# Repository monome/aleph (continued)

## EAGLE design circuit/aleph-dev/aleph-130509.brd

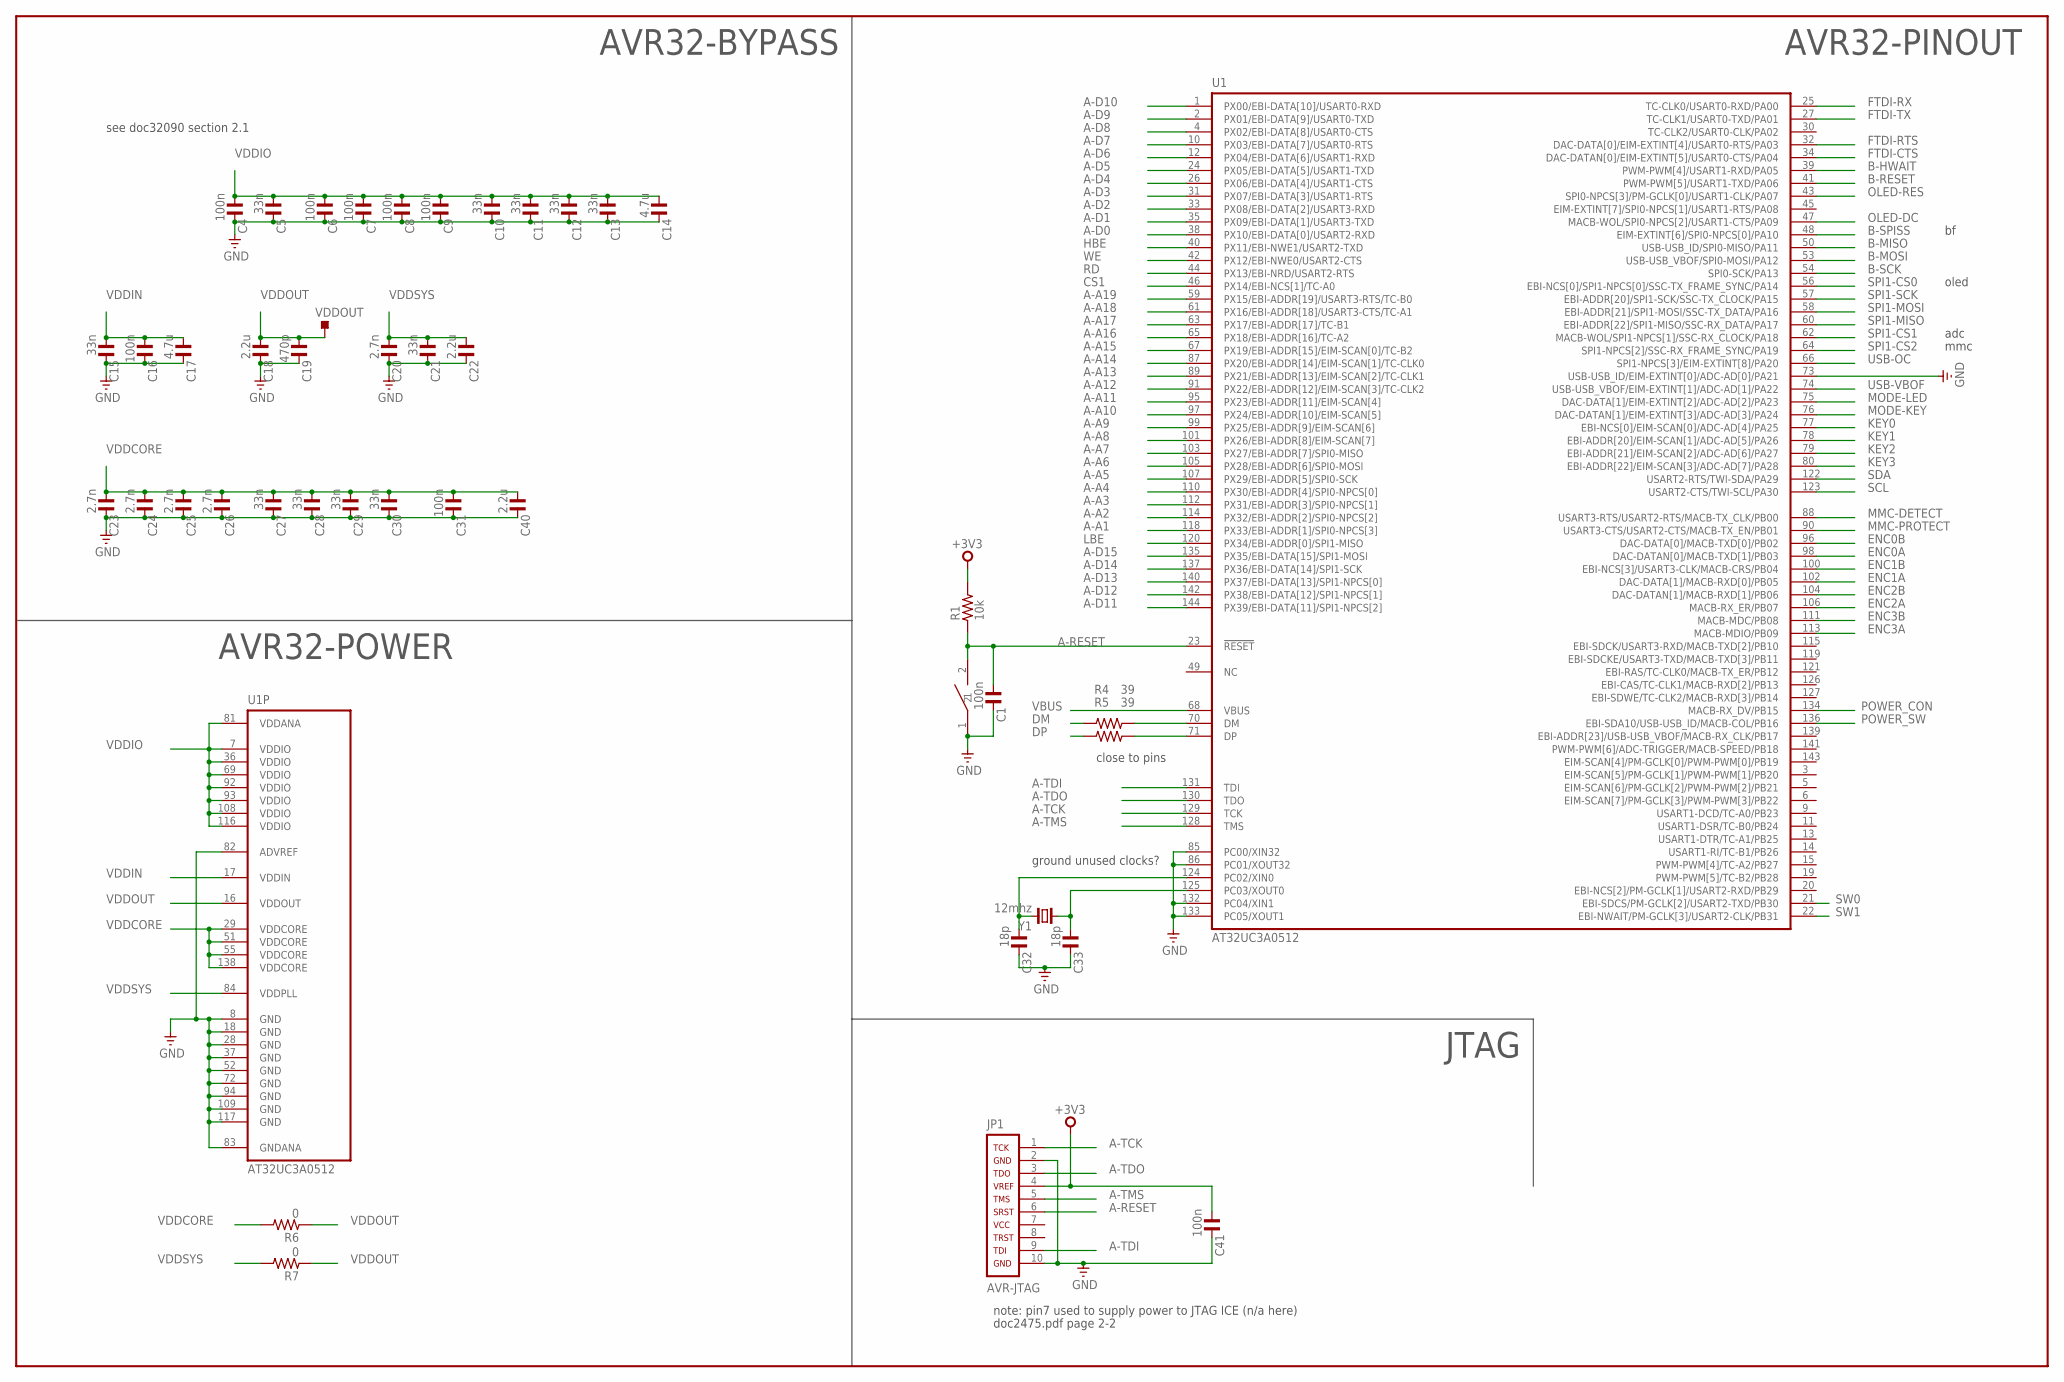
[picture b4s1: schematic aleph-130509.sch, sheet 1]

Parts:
C1, C4, C6, C7, C8, C9, C16, C31, C41: 100n; C0603
C5, C10, C11, C12, C13, C15, C21, C27, C28, C29, C30: 33n; C0603
C14, C17: 4.7u; C1206
C18, C22, C40: 2.2u; C1206
C19: 470p; C0603
C20, C23, C24, C25, C26: 2.7n; C0603
C32, C33: 18p; C0603
JP1: AVR-JTAG; AVR-JTAG-10
R1: 10k; R0603
R4, R5: 39; R0603
R6, R7: 0; R0603
U1: AT32UC3A0512; LQFP144
U$1: PANASONIC-EVQ
VDDOUT: TPS-SMD-10R; SMD-10R
Y1: 12mhz; HC49UP

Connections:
+3V3: C41.1, JP1.4, R1.2; also elsewhere on the board
A-A1: U1.118 (PX33/EBI-ADDR[1]/SPI0-NPCS[3]); also elsewhere on the board
A-A2: U1.114 (PX32/EBI-ADDR[2]/SPI0-NPCS[2]); also elsewhere on the board
A-A3: U1.112 (PX31/EBI-ADDR[3]/SPI0-NPCS[1]); also elsewhere on the board
A-A4: U1.110 (PX30/EBI-ADDR[4]/SPI0-NPCS[0]); also elsewhere on the board
A-A5: U1.107 (PX29/EBI-ADDR[5]/SPI0-SCK); also elsewhere on the board
A-A6: U1.105 (PX28/EBI-ADDR[6]/SPI0-MOSI); also elsewhere on the board
A-A7: U1.103 (PX27/EBI-ADDR[7]/SPI0-MISO); also elsewhere on the board
A-A8: U1.101 (PX26/EBI-ADDR[8]/EIM-SCAN[7]); also elsewhere on the board
A-A9: U1.99 (PX25/EBI-ADDR[9]/EIM-SCAN[6]); also elsewhere on the board
A-A10: U1.97 (PX24/EBI-ADDR[10]/EIM-SCAN[5]); also elsewhere on the board
A-A11: U1.95 (PX23/EBI-ADDR[11]/EIM-SCAN[4]); also elsewhere on the board
A-A12: U1.91 (PX22/EBI-ADDR[12]/EIM-SCAN[3]/TC-CLK2); also elsewhere on the board
A-A13: U1.89 (PX21/EBI-ADDR[13]/EIM-SCAN[2]/TC-CLK1); also elsewhere on the board
A-A14: U1.87 (PX20/EBI-ADDR[14]/EIM-SCAN[1]/TC-CLK0); also elsewhere on the board
A-A15: U1.67 (PX19/EBI-ADDR[15]/EIM-SCAN[0]/TC-B2); also elsewhere on the board
A-A16: U1.65 (PX18/EBI-ADDR[16]/TC-A2); also elsewhere on the board
A-A17: U1.63 (PX17/EBI-ADDR[17]/TC-B1); also elsewhere on the board
A-A18: U1.61 (PX16/EBI-ADDR[18]/USART3-CTS/TC-A1); also elsewhere on the board
A-A19: U1.59 (PX15/EBI-ADDR[19]/USART3-RTS/TC-B0); also elsewhere on the board
A-D0: U1.38 (PX10/EBI-DATA[0]/USART2-RXD); also elsewhere on the board
A-D1: U1.35 (PX09/EBI-DATA[1]/USART3-TXD); also elsewhere on the board
A-D2: U1.33 (PX08/EBI-DATA[2]/USART3-RXD); also elsewhere on the board
A-D3: U1.31 (PX07/EBI-DATA[3]/USART1-RTS); also elsewhere on the board
A-D4: U1.26 (PX06/EBI-DATA[4]/USART1-CTS); also elsewhere on the board
A-D5: U1.24 (PX05/EBI-DATA[5]/USART1-TXD); also elsewhere on the board
A-D6: U1.12 (PX04/EBI-DATA[6]/USART1-RXD); also elsewhere on the board
A-D7: U1.10 (PX03/EBI-DATA[7]/USART0-RTS); also elsewhere on the board
A-D8: U1.4 (PX02/EBI-DATA[8]/USART0-CTS); also elsewhere on the board
A-D9: U1.2 (PX01/EBI-DATA[9]/USART0-TXD); also elsewhere on the board
A-D10: U1.1 (PX00/EBI-DATA[10]/USART0-RXD); also elsewhere on the board
A-D11: U1.144 (PX39/EBI-DATA[11]/SPI1-NPCS[2]); also elsewhere on the board
A-D12: U1.142 (PX38/EBI-DATA[12]/SPI1-NPCS[1]); also elsewhere on the board
A-D13: U1.140 (PX37/EBI-DATA[13]/SPI1-NPCS[0]); also elsewhere on the board
A-D14: U1.137 (PX36/EBI-DATA[14]/SPI1-SCK); also elsewhere on the board
A-D15: U1.135 (PX35/EBI-DATA[15]/SPI1-MOSI); also elsewhere on the board
A-RESET: C1.1, JP1.6, R1.1, U1.23 (!RESET), U$1.2
A-TCK: JP1.1, U1.129 (TCK)
A-TDI: JP1.9, U1.131 (TDI)
A-TDO: JP1.3, U1.130 (TDO)
A-TMS: JP1.5, U1.128 (TMS)
B-HWAIT: U1.39 (PWM-PWM[4]/USART1-RXD/PA05); also elsewhere on the board
B-MISO: U1.50 (USB-USB_ID/SPI0-MISO/PA11); also elsewhere on the board
B-MOSI: U1.53 (USB-USB_VBOF/SPI0-MOSI/PA12); also elsewhere on the board
B-RESET: U1.41 (PWM-PWM[5]/USART1-TXD/PA06); also elsewhere on the board
B-SCK: U1.54 (SPI0-SCK/PA13); also elsewhere on the board
B-SPISS: U1.48 (EIM-EXTINT[6]/SPI0-NPCS[0]/PA10); also elsewhere on the board
CS1: U1.46 (PX14/EBI-NCS[1]/TC-A0); also elsewhere on the board
DM: R4.2; also elsewhere on the board
DP: R5.2; also elsewhere on the board
ENC0A: U1.98 (DAC-DATAN[0]/MACB-TXD[1]/PB03); also elsewhere on the board
ENC0B: U1.96 (DAC-DATA[0]/MACB-TXD[0]/PB02); also elsewhere on the board
ENC1A: U1.102 (DAC-DATA[1]/MACB-RXD[0]/PB05); also elsewhere on the board
ENC1B: U1.100 (EBI-NCS[3]/USART3-CLK/MACB-CRS/PB04); also elsewhere on the board
ENC2A: U1.106 (MACB-RX_ER/PB07); also elsewhere on the board
ENC2B: U1.104 (DAC-DATAN[1]/MACB-RXD[1]/PB06); also elsewhere on the board
ENC3A: U1.113 (MACB-MDIO/PB09); also elsewhere on the board
ENC3B: U1.111 (MACB-MDC/PB08); also elsewhere on the board
FTDI-CTS: U1.34 (DAC-DATAN[0]/EIM-EXTINT[5]/USART0-CTS/P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); also elsewhere on the board
FTDI-RTS: U1.32 (DAC-DATA[0]/EIM-EXTINT[4]/USART0-RTS/PA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); also elsewhere on the board
FTDI-RX: U1.25 (TC-CLK0/USART0-RXD/PA00); also elsewhere on the board
FTDI-TX: U1.27 (TC-CLK1/USART0-TXD/PA01); also elsewhere on the board
GND: C1.2, C4.2, C5.2, C6.2, C7.2, C8.2, C9.2, C10.2, C11.2, C12.2, C13.2, C14.2, C15.2, C16.2, C17.2, C18.2, C19.2, C20.2, C21.2, C22.2, C23.2, C24.2, C25.2, C26.2, C27.2, C28.2, C29.2, C30.2, C31.2, C32.2, C33.2, C40.2, C41.2, JP1.2, JP1.10, U1.8 (GND), U1.18 (GND), U1.28 (GND), U1.37 (GND), U1.52 (GND), U1.72 (GND), U1.73 (USB-USB_ID/EIM-EXTINT[0]/ADC-AD[0]/PA21), U1.82 (ADVREF), U1.83 (GNDANA), U1.85 (PC00/XIN32), U1.86 (PC01/XOUT32), U1.94 (GND), U1.109 (GND), U1.117 (GND), U1.132 (PC04/XIN1), U1.133 (PC05/XOUT1), U$1.1; also elsewhere on the board
HBE: U1.40 (PX11/EBI-NWE1/USART2-TXD); also elsewhere on the board
KEY0: U1.77 (EBI-NCS[0]/EIM-SCAN[0]/ADC-AD[4]/PA25); also elsewhere on the board
KEY1: U1.78 (EBI-ADDR[20]/EIM-SCAN[1]/ADC-AD[5]/PA26); also elsewhere on the board
KEY2: U1.79 (EBI-ADDR[21]/EIM-SCAN[2]/ADC-AD[6]/PA27); also elsewhere on the board
KEY3: U1.80 (EBI-ADDR[22]/EIM-SCAN[3]/ADC-AD[7]/PA28); also elsewhere on the board
LBE: U1.120 (PX34/EBI-ADDR[0]/SPI1-MISO); also elsewhere on the board
MMC-DETECT: U1.88 (USART3-RTS/USART2-RTS/MACB-TX_CLK/PB00); also elsewhere on the board
MMC-PROTECT: U1.90 (USART3-CTS/USART2-CTS/MACB-TX_EN/PB01); also elsewhere on the board
MODE-KEY: U1.76 (DAC-DATAN[1]/EIM-EXTINT[3]/ADC-AD[3]/PA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); also elsewhere on the board
MODE-LED: U1.75 (DAC-DATA[1]/EIM-EXTINT[2]/ADC-AD[2]/PA23); also elsewhere on the board
unnamed: C32.1, U1.124 (PC02/XIN0), Y1.2
unnamed: C33.1, U1.125 (PC03/XOUT0), Y1.1
unnamed: R4.1, U1.70 (DM)
unnamed: R5.1, U1.71 (DP)
OLED-DC: U1.47 (MACB-WOL/SPI0-NPCS[2]/USART1-CTS/PA09); also elsewhere on the board
OLED-RES: U1.43 (SPI0-NPCS[3]/PM-GCLK[0]/USART1-CLK/PA07); also elsewhere on the board
POWER_CON: U1.134 (MACB-RX_DV/PB15); also elsewhere on the board
POWER_SW: U1.136 (EBI-SDA10/USB-USB_ID/MACB-COL/PB16); also elsewhere on the board
RD: U1.44 (PX13/EBI-NRD/USART2-RTS); also elsewhere on the board
SCL: U1.123 (USART2-CTS/TWI-SCL/PA30); also elsewhere on the board
SDA: U1.122 (USART2-RTS/TWI-SDA/PA29); also elsewhere on the board
SPI1-CS0: U1.56 (EBI-NCS[0]/SPI1-NPCS[0]/SSC-TX_FRAME_SY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); also elsewhere on the board
SPI1-CS1: U1.62 (MACB-WOL/SPI1-NPCS[1]/SSC-RX_CLOCK/PA18); also elsewhere on the board
SPI1-CS2: U1.64 (SPI1-NPCS[2]/SSC-RX_FRAME_SYNC/PA19); also elsewhere on the board
SPI1-MISO: U1.60 (EBI-ADDR[22]/SPI1-MISO/SSC-RX_DATA/PA17); also elsewhere on the board
SPI1-MOSI: U1.58 (EBI-ADDR[21]/SPI1-MOSI/SSC-TX_DATA/PA16); also elsewhere on the board
SPI1-SCK: U1.57 (EBI-ADDR[20]/SPI1-SCK/SSC-TX_CLOCK/PA15); also elsewhere on the board
SW0: U1.21 (EBI-SDCS/PM-GCLK[2]/USART2-TXD/PB30); also elsewhere on the board
SW1: U1.22 (EBI-NWAIT/PM-GCLK[3]/USART2-CLK/PB31); also elsewhere on the board
USB-OC: U1.66 (SPI1-NPCS[3]/EIM-EXTINT[8]/PA20); also elsewhere on the board
USB-VBOF: U1.74 (USB-USB_VBOF/EIM-EXTINT[1]/ADC-AD[1]/PA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); also elsewhere on the board
VBUS: U1.68 (VBUS); also elsewhere on the board
VDDCORE: C23.1, C24.1, C25.1, C26.1, C27.1, C28.1, C29.1, C30.1, C31.1, C40.1, R6.2, U1.29 (VDDCORE), U1.51 (VDDCORE), U1.55 (VDDCORE), U1.138 (VDDCORE)
VDDIN: C15.1, C16.1, C17.1, U1.17 (VDDIN); also elsewhere on the board
VDDIO: C4.1, C5.1, C6.1, C7.1, C8.1, C9.1, C10.1, C11.1, C12.1, C13.1, C14.1, U1.7 (VDDIO), U1.36 (VDDIO), U1.69 (VDDIO), U1.81 (VDDANA), U1.92 (VDDIO), U1.93 (VDDIO), U1.108 (VDDIO), U1.116 (VDDIO); also elsewhere on the board
VDDOUT: C18.1, C19.1, R6.1, R7.1, U1.16 (VDDOUT), VDDOUT.TP
VDDSYS: C20.1, C21.1, C22.1, R7.2, U1.84 (VDDPLL)
WE: U1.42 (PX12/EBI-NWE0/USART2-CTS); also elsewhere on the board

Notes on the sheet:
note: pin7 used to supply power to JTAG ICE (n/a here)
doc2475.pdf page 2-2
ground unused clocks?
close to pins
see doc32090 section 2.1
mmc
adc
JTAG
AVR32-POWER
AVR32-BYPASS
AVR32-PINOUT
oled

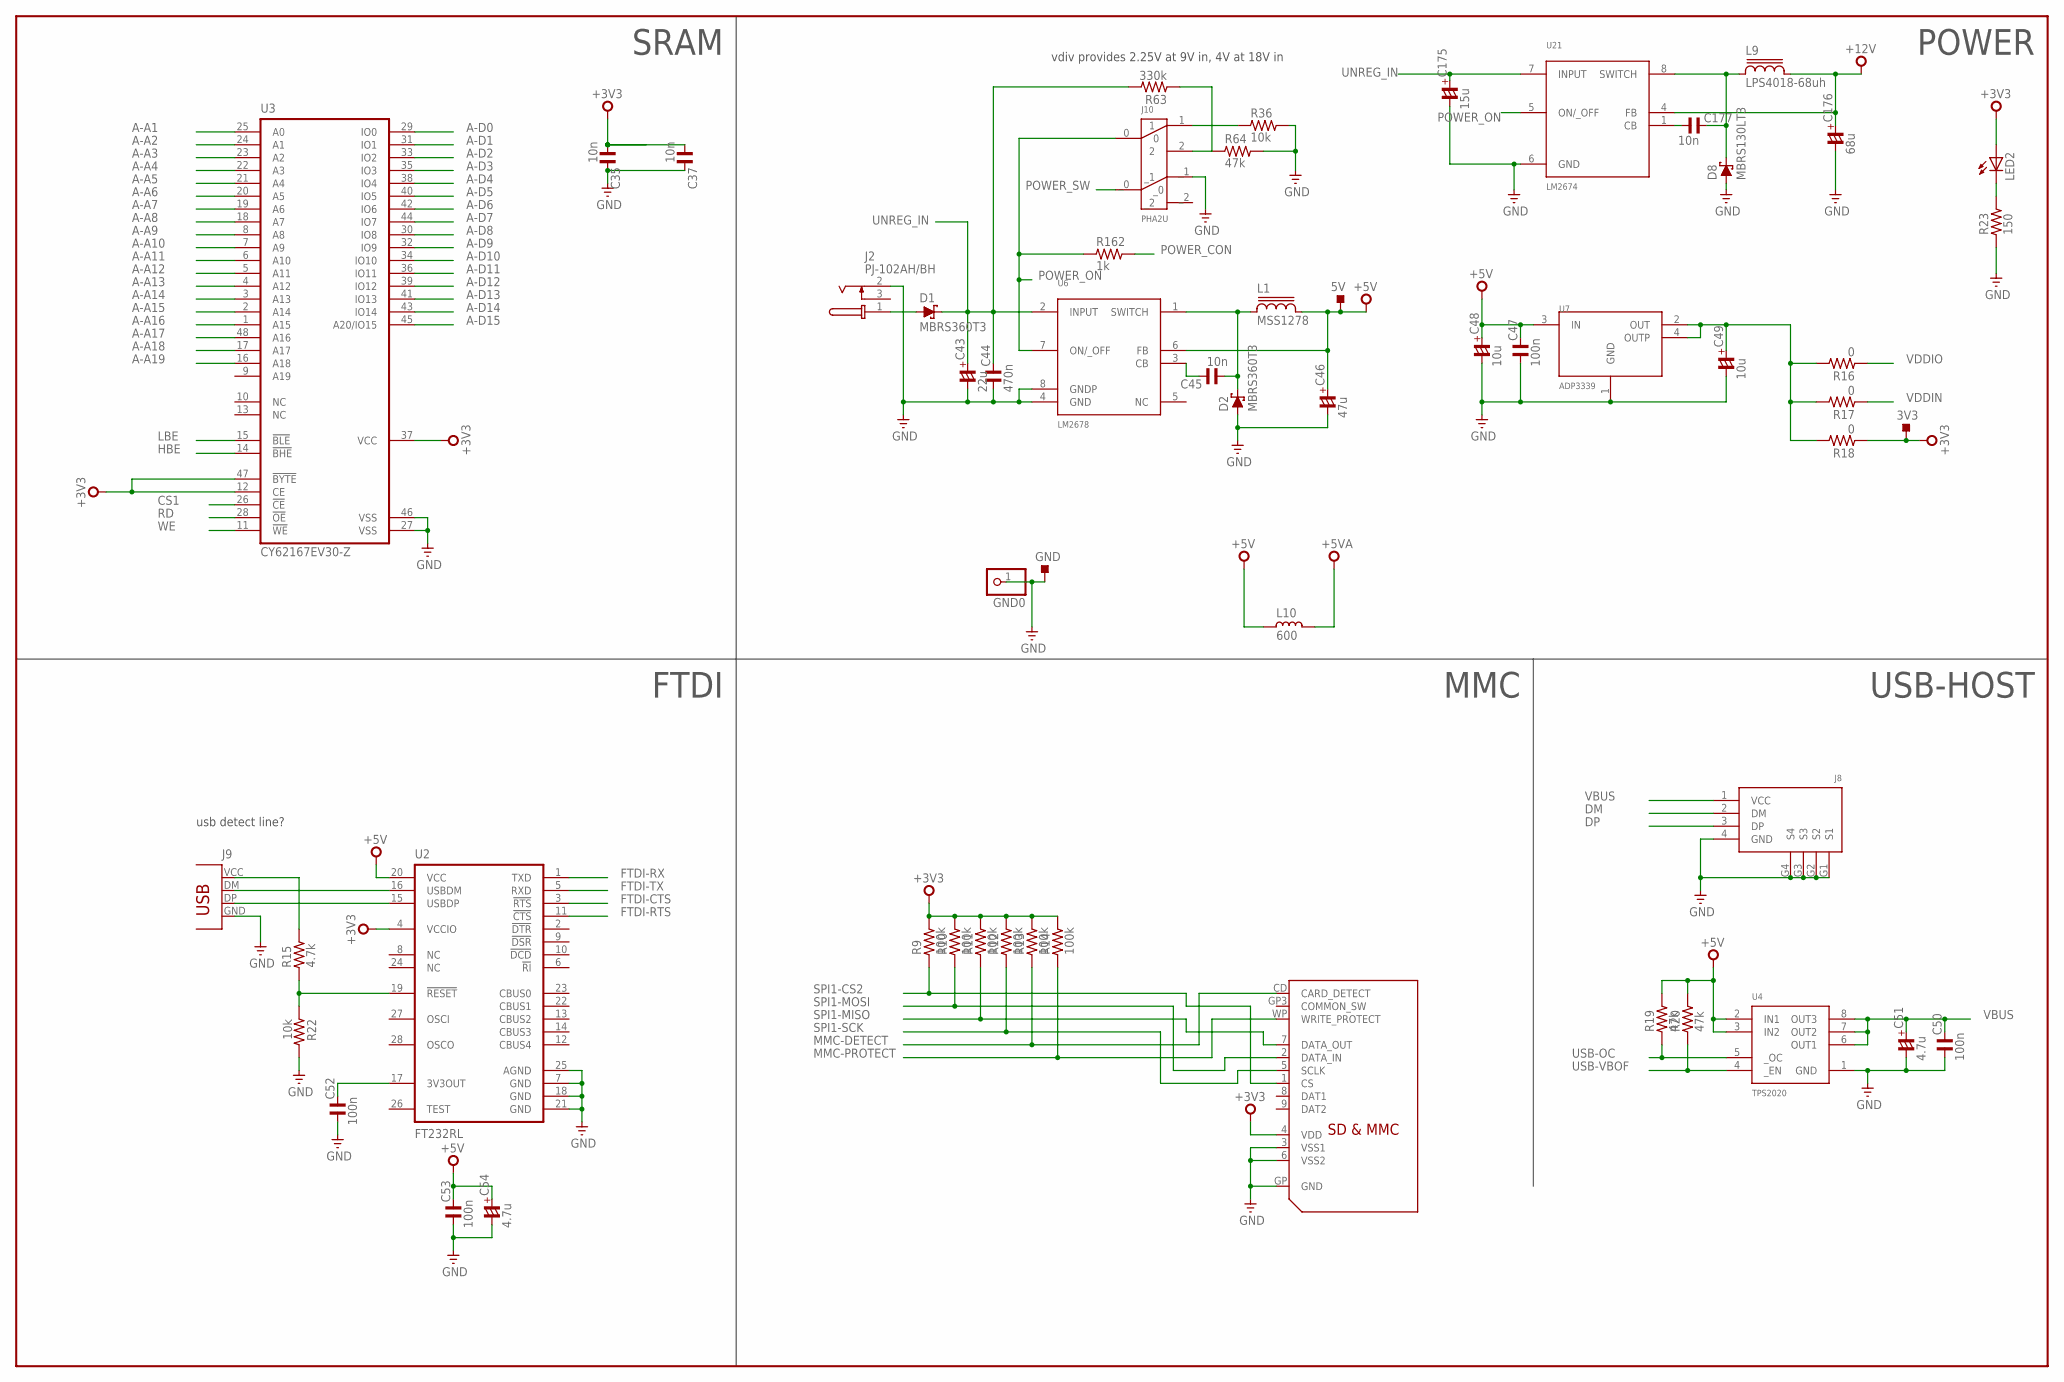
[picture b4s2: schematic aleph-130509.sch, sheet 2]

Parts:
3V3, 5V: TPS-SMD-15R; SMD-15R
C35, C37, C177: 10n; C0603
C43: 22u; C1206/T
C44: 470n; C1206
C45: 10n; C1206
C46: 47u; C3528/T
C47: 100n; C1206
C48, C49: 10u; C1206/T
C50, C52, C53: 100n; C0603
C51, C54: 4.7u; C1206/T
C175: 15u; C6032/T
C176: 68u; C7343/T
D1, D2: MBRS360T3; SMC
D8: MBRS130LT3; SMB403A
GND: TPS-SMD-20R; SMD-20R
GND0: PINHD-1X1; 1X01
J2: PJ-102AH/BH; PJ-102XH
J8: USBA-VERT
J9: USB_TYPE_B; USB_B
J10: PHA2U
L1: MSS1278
L9: LPS4018-68uh; LPS4018
L10: 600; L1206
LED2: LEDCHIPLED_1206; CHIPLED_1206
R9, R10, R11, R12, R13, R14: 100k; R0603
R15: 4.7k; R0603
R16, R17, R18: 0; R0603
R19, R20, R64: 47k; R0603
R22, R36: 10k; R0603
R23: 150; R0603
R63: 330k; R0603
R162: 1k; R0603
U2: FT232RL; SSOP28
U3: CY62167EV30-Z; TSOP48
U4: TPS2020; SO08
U6: LM2678; TO263-7
U7: ADP3339; SOT223
U21: LM2674; SO08
U$6: SDMMC06132; 06132

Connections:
+3V3: 3V3.TP, C35.1, C37.1, LED2.A, R9.2, R10.2, R11.2, R12.2, R13.2, R14.2, R18.1, U2.4 (VCCIO), U3.12 (CE), U3.37 (VCC), U3.47 (!BYTE!), U$6.4 (VDD); also elsewhere on the board
+5V: 5V.TP, C46.+, C47.2, C48.+, C53.2, C54.+, L1.2, L10.2, R19.2, R20.2, U2.20 (VCC), U4.2 (IN1), U4.3 (IN2), U6.6 (FB), U7.3 (IN); also elsewhere on the board
+5VA: L10.1; also elsewhere on the board
+12V: C176.+, L9.2, U21.4 (FB); also elsewhere on the board
A-A1: U3.25 (A0); also elsewhere on the board
A-A2: U3.24 (A1); also elsewhere on the board
A-A3: U3.23 (A2); also elsewhere on the board
A-A4: U3.22 (A3); also elsewhere on the board
A-A5: U3.21 (A4); also elsewhere on the board
A-A6: U3.20 (A5); also elsewhere on the board
A-A7: U3.19 (A6); also elsewhere on the board
A-A8: U3.18 (A7); also elsewhere on the board
A-A9: U3.8 (A8); also elsewhere on the board
A-A10: U3.7 (A9); also elsewhere on the board
A-A11: U3.6 (A10); also elsewhere on the board
A-A12: U3.5 (A11); also elsewhere on the board
A-A13: U3.4 (A12); also elsewhere on the board
A-A14: U3.3 (A13); also elsewhere on the board
A-A15: U3.2 (A14); also elsewhere on the board
A-A16: U3.1 (A15); also elsewhere on the board
A-A17: U3.48 (A16); also elsewhere on the board
A-A18: U3.17 (A17); also elsewhere on the board
A-A19: U3.16 (A18); also elsewhere on the board
A-D0: U3.29 (IO0); also elsewhere on the board
A-D1: U3.31 (IO1); also elsewhere on the board
A-D2: U3.33 (IO2); also elsewhere on the board
A-D3: U3.35 (IO3); also elsewhere on the board
A-D4: U3.38 (IO4); also elsewhere on the board
A-D5: U3.40 (IO5); also elsewhere on the board
A-D6: U3.42 (IO6); also elsewhere on the board
A-D7: U3.44 (IO7); also elsewhere on the board
A-D8: U3.30 (IO8); also elsewhere on the board
A-D9: U3.32 (IO9); also elsewhere on the board
A-D10: U3.34 (IO10); also elsewhere on the board
A-D11: U3.36 (IO11); also elsewhere on the board
A-D12: U3.39 (IO12); also elsewhere on the board
A-D13: U3.41 (IO13); also elsewhere on the board
A-D14: U3.43 (IO14); also elsewhere on the board
A-D15: U3.45 (A20/IO15); also elsewhere on the board
CS1: U3.26 (!CE!); also elsewhere on the board
DM: J8.2 (DM); also elsewhere on the board
DP: J8.3 (DP); also elsewhere on the board
FTDI-CTS: U2.3 (!RTS!); also elsewhere on the board
FTDI-RTS: U2.11 (!CTS!); also elsewhere on the board
FTDI-RX: U2.1 (TXD); also elsewhere on the board
FTDI-TX: U2.5 (RXD); also elsewhere on the board
GND: C35.2, C37.2, C43.-, C44.1, C46.-, C47.1, C48.-, C49.-, C50.1, C51.-, C52.1, C53.1, C54.-, C175.-, C176.-, D2.A, D8.A, GND.TP, GND0.1, J2.2 (S), J8.4 (GND), J8.G1 (S1), J8.G2 (S2), J8.G3 (S3), J8.G4 (S4), J9.GND, J10._1, R22.2, R23.1, R36.2, R64.2, U2.7 (GND), U2.18 (GND), U2.21 (GND), U2.25 (AGND), U3.27 (VSS), U3.46 (VSS), U4.1 (GND), U6.4 (GND), U6.8 (GNDP), U7.1 (GND), U21.6 (GND), U$6.3 (VSS1), U$6.6 (VSS2), U$6.GP (GND); also elsewhere on the board
HBE: U3.14 (!BHE!); also elsewhere on the board
LBE: U3.15 (!BLE!); also elsewhere on the board
MMC-DETECT: R13.1, U$6.CD (CARD_DETECT); also elsewhere on the board
MMC-PROTECT: R14.1, U$6.WP (WRITE_PROTECT); also elsewhere on the board
unnamed: D1.A, J2.1 (T)
unnamed: R15.1, R22.1, U2.19 (!RESET!)
unnamed: C45.1, D2.C, L1.1, U6.1 (SWITCH)
unnamed: C45.2, U6.3 (CB)
unnamed: J9.DM (USBDM), U2.16 (USBDM)
unnamed: J9.DP (USBDP), U2.15 (USBDP)
unnamed: C52.2, U2.17 (3V3OUT)
unnamed: LED2.C, R23.2
unnamed: J9.VCC, R15.2
unnamed: C49.+, R16.2, R17.2, R18.2, U7.2 (OUT), U7.4 (OUTP)
unnamed: J10.1, R36.1
unnamed: J10.2, R63.1, R64.1
unnamed: C177.1, U21.1 (CB)
unnamed: C177.2, D8.C, L9.1, U21.8 (SWITCH)
POWER_CON: R162.2; also elsewhere on the board
POWER_ON: J10.0, R162.1, U6.7 (ON/_OFF), U21.5 (ON/_OFF)
POWER_SW: J10._0; also elsewhere on the board
RD: U3.28 (!OE!); also elsewhere on the board
SPI1-CS2: R9.1, U$6.1 (CS); also elsewhere on the board
SPI1-MISO: R11.1, U$6.7 (DATA_OUT); also elsewhere on the board
SPI1-MOSI: R10.1, U$6.2 (DATA_IN); also elsewhere on the board
SPI1-SCK: R12.1, U$6.5 (SCLK); also elsewhere on the board
UNREG_IN: C43.+, C44.2, C175.+, D1.C, R63.2, U6.2 (INPUT), U21.7 (INPUT)
USB-OC: R19.1, U4.5 (_OC); also elsewhere on the board
USB-VBOF: R20.1, U4.4 (_EN); also elsewhere on the board
VBUS: C50.2, C51.+, J8.1 (VCC), U4.6 (OUT1), U4.7 (OUT2), U4.8 (OUT3); also elsewhere on the board
VDDIN: R17.1; also elsewhere on the board
VDDIO: R16.1; also elsewhere on the board
WE: U3.11 (!WE!); also elsewhere on the board

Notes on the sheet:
usb detect line?
SRAM
MMC
USB-HOST
FTDI
vdiv provides 2.25V at 9V in, 4V at 18V in
POWER

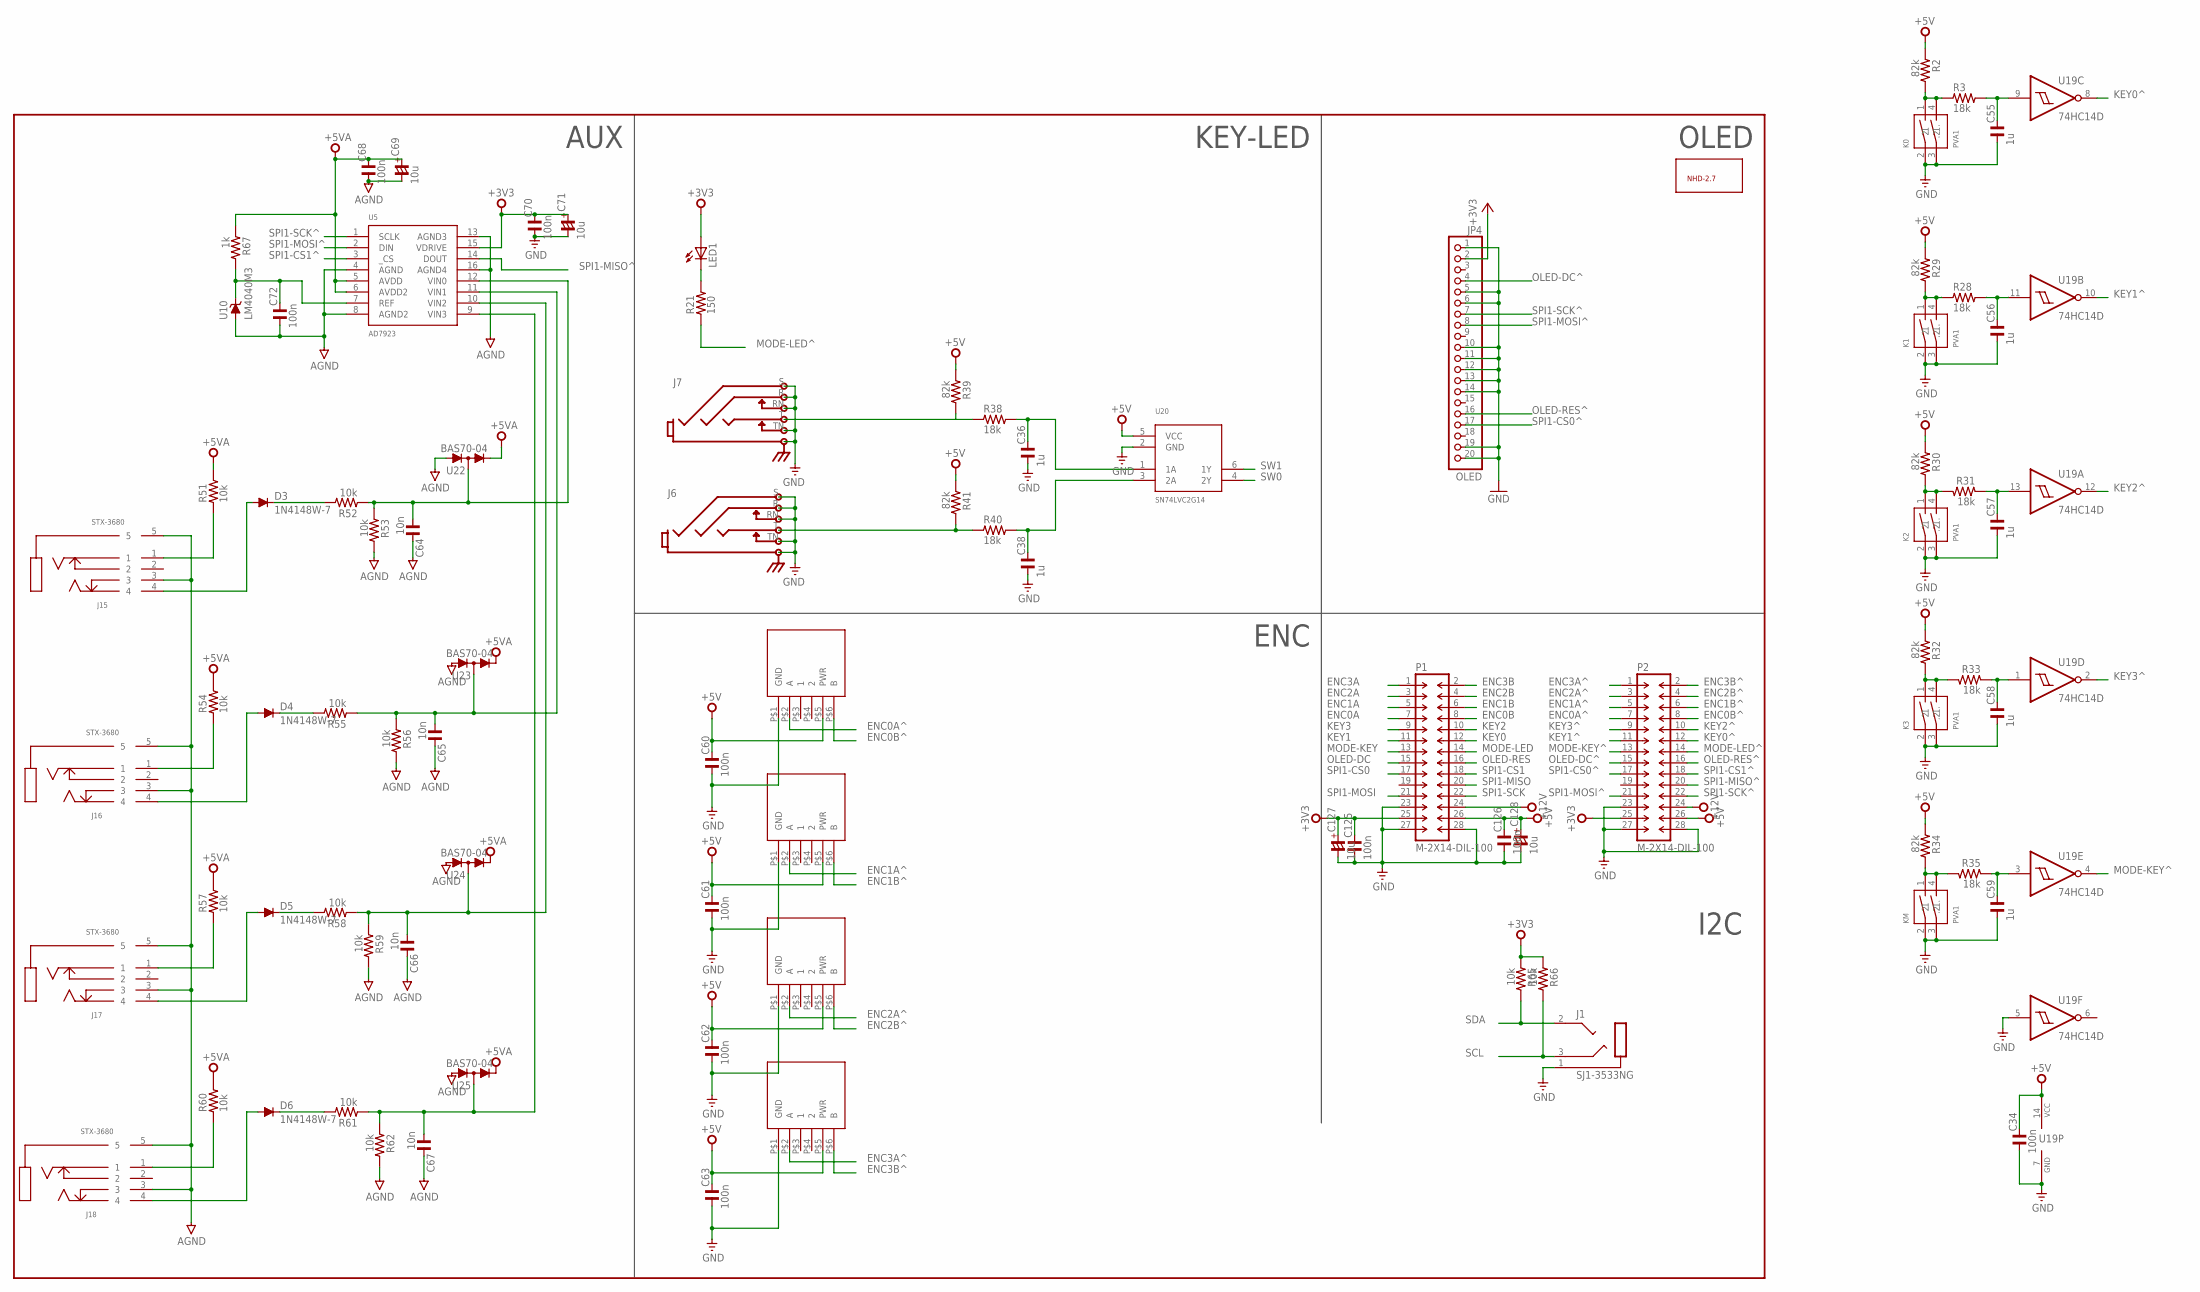
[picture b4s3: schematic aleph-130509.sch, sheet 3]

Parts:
C34, C60, C61, C62, C63, C68, C70, C72, C125, C126: 100n; C0603
C36, C38, C55, C56, C57, C58, C59: 1u; C0603
C64, C65, C66, C67: 10n; C0603
C69, C71, C127, C128: 10u; C1206/T
D3, D4, D5, D6: 1N4148W-7; SOD123
J1: SJ1-3533NG
J6, J7: STEREOSW2GND; NEUTRIK-NRJ6HM-1
J15, J16, J17, J18: STX-3680
JP4: OLED; 1X20
K0, K1, K2, K3: PVA1
KM: PVA1
LED1: LEDCHIPLED_1206; CHIPLED_1206
P1, P2: M-2X14-DIL-100; DIL-100-2X14
R2, R29, R30, R32, R34, R39, R41: 82k; R0603
R3, R28, R31, R33, R35, R38, R40: 18k; R0603
R21: 150; R0603
R51, R52, R53, R54, R55, R56, R57, R58, R59, R60, R61, R62, R65, R66: 10k; R0603
R67: 1k; R0603
U5: AD7923; TSSOP16
U10: LM4040M3; SOT23
U19: 74HC14D; SO14
U20: SN74LVC2G14; SOT23-6
U22, U23, U24, U25: BAS70-04; SOT23
U$2, U$3, U$4, U$5: BOURNS-EM14
U$10: NHD-2.7

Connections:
+3V3: C70.2, C71.+, C125.2, C127.+, JP4.2, LED1.A, P1.25, P2.25, R65.1, R66.1, U5.15 (VDRIVE); also elsewhere on the board
+5V: C34.2, C60.2, C61.2, C62.2, C63.2, C126.2, C128.+, P1.26, P2.26, R2.1, R29.1, R30.1, R32.1, R34.1, R39.1, R41.1, U19.14 (VCC), U20.5 (VCC), U$2.P$5 (PWR), U$3.P$5 (PWR), U$4.P$5 (PWR), U$5.P$5 (PWR); also elsewhere on the board
+5VA: C68.2, C69.+, R51.2, R54.2, R57.2, R60.2, R67.1, U5.5 (AVDD), U5.6 (AVDD2), U22.2 (C), U23.2 (C), U24.2 (C), U25.2 (C); also elsewhere on the board
+12V: P1.24, P2.24; also elsewhere on the board
AGND: C64.2, C65.2, C66.2, C67.2, C68.1, C69.-, C72.1, J15.3, J15.5, J16.3, J16.5, J17.3, J17.5, J18.3, J18.5, R53.2, R56.2, R59.2, R62.2, U5.4 (AGND), U5.8 (AGND2), U5.13 (AGND3), U5.16 (AGND4), U10.2 (A), U22.1 (A), U23.1 (A), U24.1 (A), U25.1 (A); also elsewhere on the board
ENC0A: P1.7; also elsewhere on the board
ENC0A^: P2.7, U$2.P$2 (A)
ENC0B: P1.8; also elsewhere on the board
ENC0B^: P2.8, U$2.P$6 (B)
ENC1A: P1.5; also elsewhere on the board
ENC1A^: P2.5, U$3.P$2 (A)
ENC1B: P1.6; also elsewhere on the board
ENC1B^: P2.6, U$3.P$6 (B)
ENC2A: P1.3; also elsewhere on the board
ENC2A^: P2.3, U$4.P$2 (A)
ENC2B: P1.4; also elsewhere on the board
ENC2B^: P2.4, U$4.P$6 (B)
ENC3A: P1.1; also elsewhere on the board
ENC3A^: P2.1, U$5.P$2 (A)
ENC3B: P1.2; also elsewhere on the board
ENC3B^: P2.2, U$5.P$6 (B)
GND: C34.1, C36.1, C38.1, C55.1, C56.1, C57.1, C58.1, C59.1, C60.1, C61.1, C62.1, C63.1, C70.1, C71.-, C125.1, C126.1, C127.-, C128.-, J1.1 (S), J6.R, J6.RN, J6.S, J6.TN, J7.R, J7.RN, J7.S, J7.TN, JP4.1, JP4.5, JP4.6, JP4.10, JP4.11, JP4.12, JP4.13, JP4.14, JP4.19, JP4.20, K0.2 (1), K0.3 (1.), K1.2 (1), K1.3 (1.), K2.2 (1), K2.3 (1.), K3.2 (1), K3.3 (1.), KM.2 (1), KM.3 (1.), P1.23, P1.27, P1.28, P2.23, P2.27, P2.28, U19.5 (I), U19.7 (GND), U20.2 (GND), U$2.P$1 (GND), U$3.P$1 (GND), U$4.P$1 (GND), U$5.P$1 (GND); also elsewhere on the board
KEY0: P1.12; also elsewhere on the board
KEY0^: P2.12, U19.8 (O)
KEY1: P1.11; also elsewhere on the board
KEY1^: P2.11, U19.10 (O)
KEY2: P1.10; also elsewhere on the board
KEY2^: P2.10, U19.12 (O)
KEY3: P1.9; also elsewhere on the board
KEY3^: P2.9, U19.2 (O)
MODE-KEY: P1.13; also elsewhere on the board
MODE-KEY^: P2.13, U19.4 (O)
MODE-LED: P1.14; also elsewhere on the board
MODE-LED^: P2.14, R21.1
unnamed: K0.1 (2), K0.4 (.2), R2.2, R3.1
unnamed: C55.2, R3.2, U19.9 (I)
unnamed: K1.1 (2), K1.4 (.2), R28.1, R29.2
unnamed: C56.2, R28.2, U19.11 (I)
unnamed: LED1.C, R21.2
unnamed: K2.1 (2), K2.4 (.2), R30.2, R31.2
unnamed: C57.2, R31.1, U19.13 (I)
unnamed: K3.1 (2), K3.4 (.2), R32.2, R33.2
unnamed: C58.2, R33.1, U19.1 (I)
unnamed: J17.1, R57.1
unnamed: D3.A, J15.4
unnamed: D4.C, R55.2
unnamed: D3.C, R52.2
unnamed: D5.C, R58.2
unnamed: J16.1, R54.1
unnamed: D4.A, J16.4
unnamed: KM.1 (2), KM.4 (.2), R34.2, R35.2
unnamed: D6.C, R61.2
unnamed: J15.1, R51.1
unnamed: D5.A, J17.4
unnamed: C59.2, R35.1, U19.3 (I)
unnamed: J18.1, R60.1
unnamed: D6.A, J18.4
unnamed: C38.2, R40.2, U20.3 (2A)
unnamed: C72.2, R67.2, U5.7 (REF), U10.1 (C)
unnamed: C65.1, R55.1, R56.1, U5.11 (VIN1), U23.3 (AC)
unnamed: C66.1, R58.1, R59.1, U5.10 (VIN2), U24.3 (AC)
unnamed: C67.1, R61.1, R62.1, U5.9 (VIN3), U25.3 (AC)
unnamed: C64.1, R52.1, R53.1, U5.12 (VIN0), U22.3 (AC)
unnamed: C36.2, R38.2, U20.1 (1A)
OLED-DC: P1.15; also elsewhere on the board
OLED-DC^: JP4.4, P2.15
OLED-RES: P1.16; also elsewhere on the board
OLED-RES^: JP4.16, P2.16
SCL: J1.3 (R), R66.2; also elsewhere on the board
SDA: J1.2 (T), R65.2; also elsewhere on the board
SPI1-CS0: P1.17; also elsewhere on the board
SPI1-CS0^: JP4.17, P2.17
SPI1-CS1: P1.18; also elsewhere on the board
SPI1-CS1^: P2.18, U5.3 (_CS)
SPI1-MISO: P1.20; also elsewhere on the board
SPI1-MISO^: P2.20, U5.14 (DOUT)
SPI1-MOSI: P1.21; also elsewhere on the board
SPI1-MOSI^: JP4.8, P2.21, U5.2 (DIN)
SPI1-SCK: P1.22; also elsewhere on the board
SPI1-SCK^: JP4.7, P2.22, U5.1 (SCLK)
SW0: U20.4 (2Y); also elsewhere on the board
SW0CON^: J7.T, R38.1, R39.2
SW1: U20.6 (1Y); also elsewhere on the board
SW1CON^: J6.T, R40.1, R41.2

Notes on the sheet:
I2C
OLED
KEY-LED
AUX
ENC
